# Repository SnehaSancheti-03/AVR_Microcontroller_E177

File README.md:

# AVR_Microcontroller  
**ATmega-Based AVR Controller PCB Design**

---

## 👩‍🎓 Student Information
- **Name:** Sneha Sancheti  
- **Roll No:** E177  

---

## 📌 Project Overview
This project presents the design and development of a complete **ATmega-based AVR microcontroller controller board** using KiCad PCB design tools.

The board integrates all essential subsystems required for embedded system prototyping, including regulated power supply, clock generation, reset circuitry, programming interface, sensor connectivity, communication interface, and peripheral headers.

The design enables reliable deployment of AVR-based embedded applications in academic and experimental environments.

---

## 🎯 Objectives
- Design a standalone AVR microcontroller PCB  
- Implement stable regulated power supply  
- Provide programming and communication interfaces  
- Support sensor and actuator connectivity  
- Integrate LCD display interface  
- Produce manufacturable PCB layout  

---

## 🧩 System Architecture
The AVR controller board is composed of the following functional blocks:

- Power Supply Section  
- ATmega Microcontroller Core  
- Clock Circuit  
- Reset Circuit  
- Programming Interface (ISP)  
- Sensor Interfaces  
- Display Interface  
- Communication Interface  
- Expansion Headers  

These modules together form a complete embedded controller platform.

---

## 🔌 Hardware Design

### ATmega Microcontroller Core
The central controller is an ATmega AVR microcontroller configured with decoupling capacitors and I/O breakout headers to support external peripherals and modules.

---

### Power Supply Section
The circuit includes a regulated DC supply stage providing stable operating voltage to the microcontroller and connected peripherals. Filtering and decoupling ensure noise-free operation.

---

### Clock Circuit
An external crystal oscillator with load capacitors provides precise timing required for accurate AVR operation.

---

### Reset Circuit
A hardware reset push-button with pull-up configuration enables proper initialization and safe restart of the microcontroller.

---

### Programming Interface
The design includes an AVR ISP programming header enabling in-system firmware uploading without removing the microcontroller from the PCB.

---

## 📟 Peripheral Interfaces

### Sensor Interfaces
The controller supports interfacing of multiple analog and digital sensors through ADC and GPIO pins, including:

- Flex sensor  
- Pressure sensor  
- Ultrasonic sensor  
- IR sensor modules  
- Analog sensor modules  

---

### Display Interface
A standard **16×2 LCD interface** is provided for real-time data visualization and system feedback.

---

### Communication Interface
UART serial communication support enables connection to external systems such as:

- USB-to-Serial converters  
- Computers  
- Embedded communication modules  

---

### Actuator / Output Interfaces
The board supports control of external devices such as:

- Motors  
- Relays  
- Buzzers  
- LEDs  
- Driver modules  

---

## 🖥️ Design Output
The project deliverables include:

- Complete schematic design  
- PCB layout  
- Gerber manufacturing files  
- Drill files  
- Component mapping files  

---

## 🛠️ Tools Used
- **KiCad** – Schematic and PCB design  
- AVR microcontroller architecture references  
- Standard electronic components  

---

## 📁 Repository Contents

Drill_files/
Gerber_Files/
AVR_Controller_E177_Sneha.kicad_pcb
AVR_Controller_E177_Sneha.kicad_sch
AVR_Controller_E177_Sneha.kicad_prl
AVR_Controller_E177_Sneha.kicad_pro

---

## 🧪 Applications
The designed AVR controller board can be used for:

- Embedded systems learning  
- Sensor interfacing experiments  
- Robotics control platforms  
- Data acquisition systems  
- Automation prototypes  
- IoT hardware projects  

---

## ✅ Conclusion
A complete AVR microcontroller controller board was successfully designed integrating power management, processing, communication, and interfacing subsystems.

The PCB layout is compact, functional, and suitable for embedded system prototyping and academic applications.

---

## 📚 Reference
ATmega AVR architecture and interfacing concepts as illustrated in the assignment design sheet.   

---

## 👤 Author
**Sneha Sancheti**  
Roll No: E177  

---

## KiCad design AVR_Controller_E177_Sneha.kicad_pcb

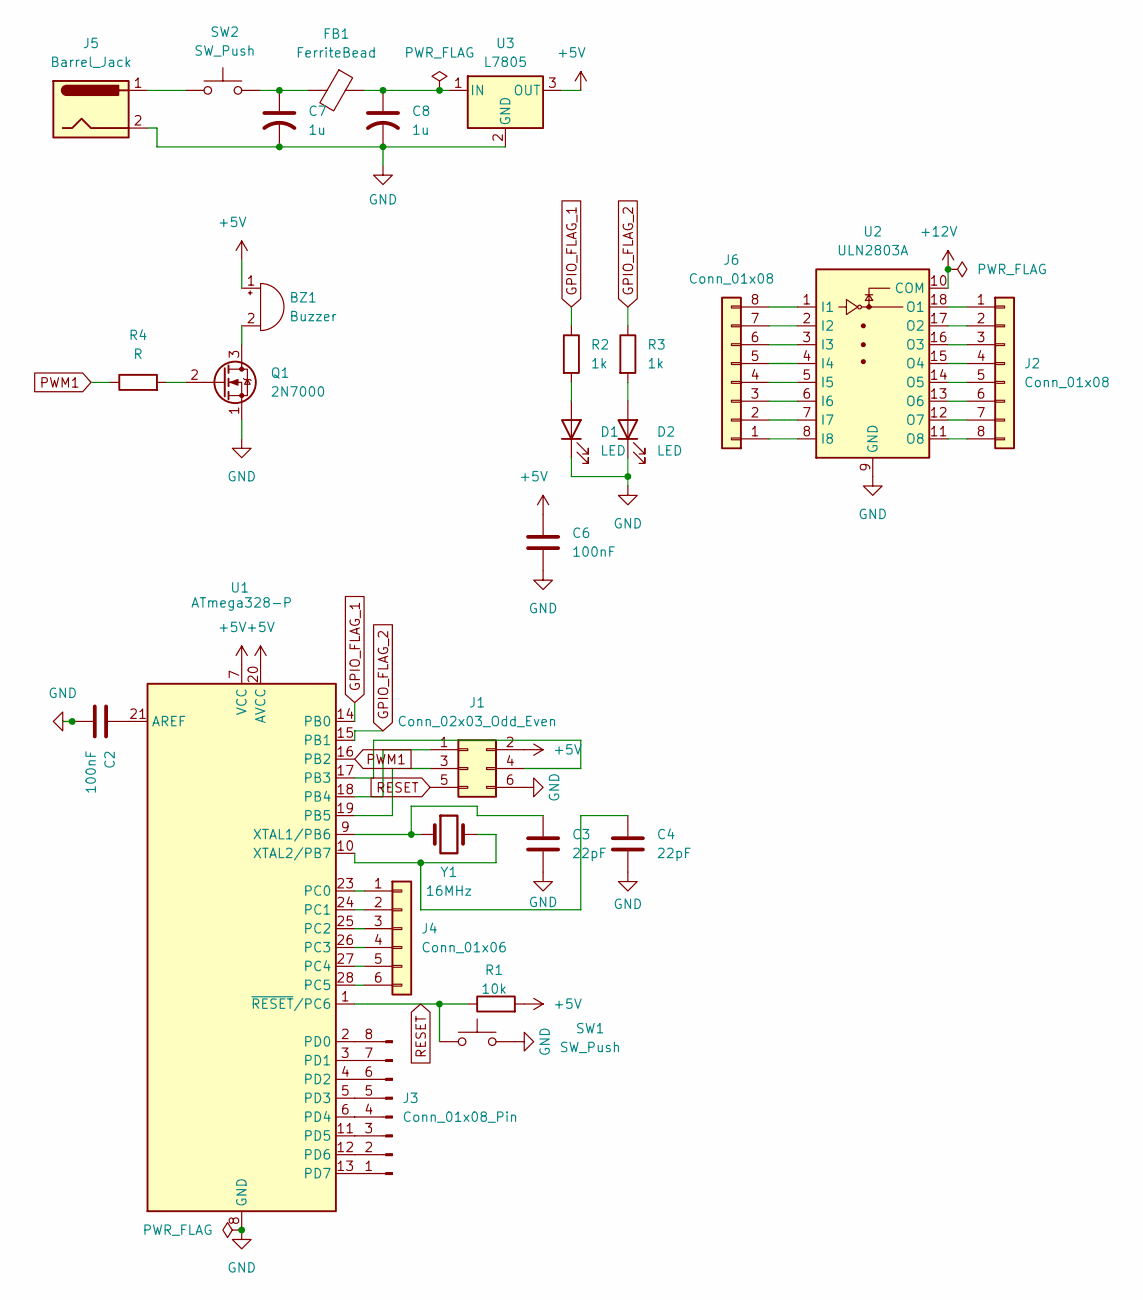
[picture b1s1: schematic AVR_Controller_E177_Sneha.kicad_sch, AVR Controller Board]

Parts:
BZ1: Buzzer; Buzzer_15x7.5RM7.6
C2, C6: 100nF; C_Disc_D5.0mm_W2.5mm_P5.00mm
C3, C4: 22pF; C_Disc_D5.0mm_W2.5mm_P5.00mm
C7, C8: 1u; C_Disc_D5.0mm_W2.5mm_P5.00mm
D1, D2: LED; LED_D3.0mm
FB1: FerriteBead; LairdTech_28C0236-0JW-10
J1: Conn_02x03_Odd_Even; PinHeader_2x03_P2.54mm_Vertical
J2, J6: Conn_01x08; PinHeader_1x08_P2.54mm_Vertical
J3: Conn_01x08_Pin; PinHeader_1x08_P2.54mm_Vertical
J4: Conn_01x06; PinHeader_1x06_P2.54mm_Vertical
J5: Barrel_Jack; BarrelJack_Horizontal
Q1: 2N7000; TO-92_Inline
R1: 10k; R_Axial_DIN0207_L6.3mm_D2.5mm_P10.16mm_Horizontal
R2, R3: 1k; R_Axial_DIN0207_L6.3mm_D2.5mm_P10.16mm_Horizontal
R4: R; R_Axial_DIN0207_L6.3mm_D2.5mm_P10.16mm_Horizontal
SW1, SW2: SW_Push; SW_PUSH_6mm
U1: ATmega328-P; DIP-28_W7.62mm
U2: ULN2803A; SOIC-18W_7.5x11.6mm_P1.27mm
U3: L7805; TO-220-3_Vertical
Y1: 16MHz; Crystal_HC49-4H_Vertical

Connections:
+5V: BZ1.1 (+), C6.2, J1.2, R1.2, U1.7 (VCC), U1.20 (AVCC), U3.3 (OUT)
+12V: U2.10 (COM)
GND: C2.1, C3.2, C4.2, C6.1, C7.2, C8.2, D1.1 (K), D2.1 (K), J1.6, J5.2, Q1.1 (S), SW1.2, U1.8 (GND), U1.22 (GND), U2.9 (GND), U3.2 (GND)
GPIO_FLAG_1: R2.1, U1.14 (PB0)
GPIO_FLAG_2: R3.1, U1.15 (PB1)
unnamed: BZ1.2 (-), Q1.3 (D)
unnamed: C7.1, FB1.2, SW2.2
unnamed: D1.2 (A), R2.2
unnamed: D2.2 (A), R3.2
unnamed: J1.1, U1.18 (PB4)
unnamed: J1.3, U1.19 (PB5)
unnamed: J1.4, U1.17 (PB3)
unnamed: J2.1, U2.18 (O1)
unnamed: J2.2, U2.17 (O2)
unnamed: J2.3, U2.16 (O3)
unnamed: J2.4, U2.15 (O4)
unnamed: J2.5, U2.14 (O5)
unnamed: J2.6, U2.13 (O6)
unnamed: J2.7, U2.12 (O7)
unnamed: J2.8, U2.11 (O8)
unnamed: J3.1, U1.13 (PD7)
unnamed: J3.2, U1.12 (PD6)
unnamed: J3.3, U1.11 (PD5)
unnamed: J3.4, U1.6 (PD4)
unnamed: J3.5, U1.5 (PD3)
unnamed: J3.6, U1.4 (PD2)
unnamed: J3.7, U1.3 (PD1)
unnamed: J3.8, U1.2 (PD0)
unnamed: J4.1, U1.23 (PC0)
unnamed: J4.2, U1.24 (PC1)
unnamed: J4.3, U1.25 (PC2)
unnamed: J4.4, U1.26 (PC3)
unnamed: J4.5, U1.27 (PC4)
unnamed: J4.6, U1.28 (PC5)
unnamed: J5.1, SW2.1
unnamed: J6.1, U2.8 (I8)
unnamed: J6.2, U2.7 (I7)
unnamed: J6.3, U2.6 (I6)
unnamed: J6.4, U2.5 (I5)
unnamed: J6.5, U2.4 (I4)
unnamed: J6.6, U2.3 (I3)
unnamed: J6.7, U2.2 (I2)
unnamed: J6.8, U2.1 (I1)
unnamed: Q1.2 (G), R4.2
unnamed: C2.2, U1.21 (AREF)
unnamed: C3.1, U1.9 (XTAL1/PB6), Y1.1
unnamed: C4.1, U1.10 (XTAL2/PB7), Y1.2
unnamed: C8.1, FB1.1, U3.1 (IN)
PWM1: R4.1, U1.16 (PB2)
RESET: J1.5, R1.1, SW1.1, U1.1 (~RESET/PC6)

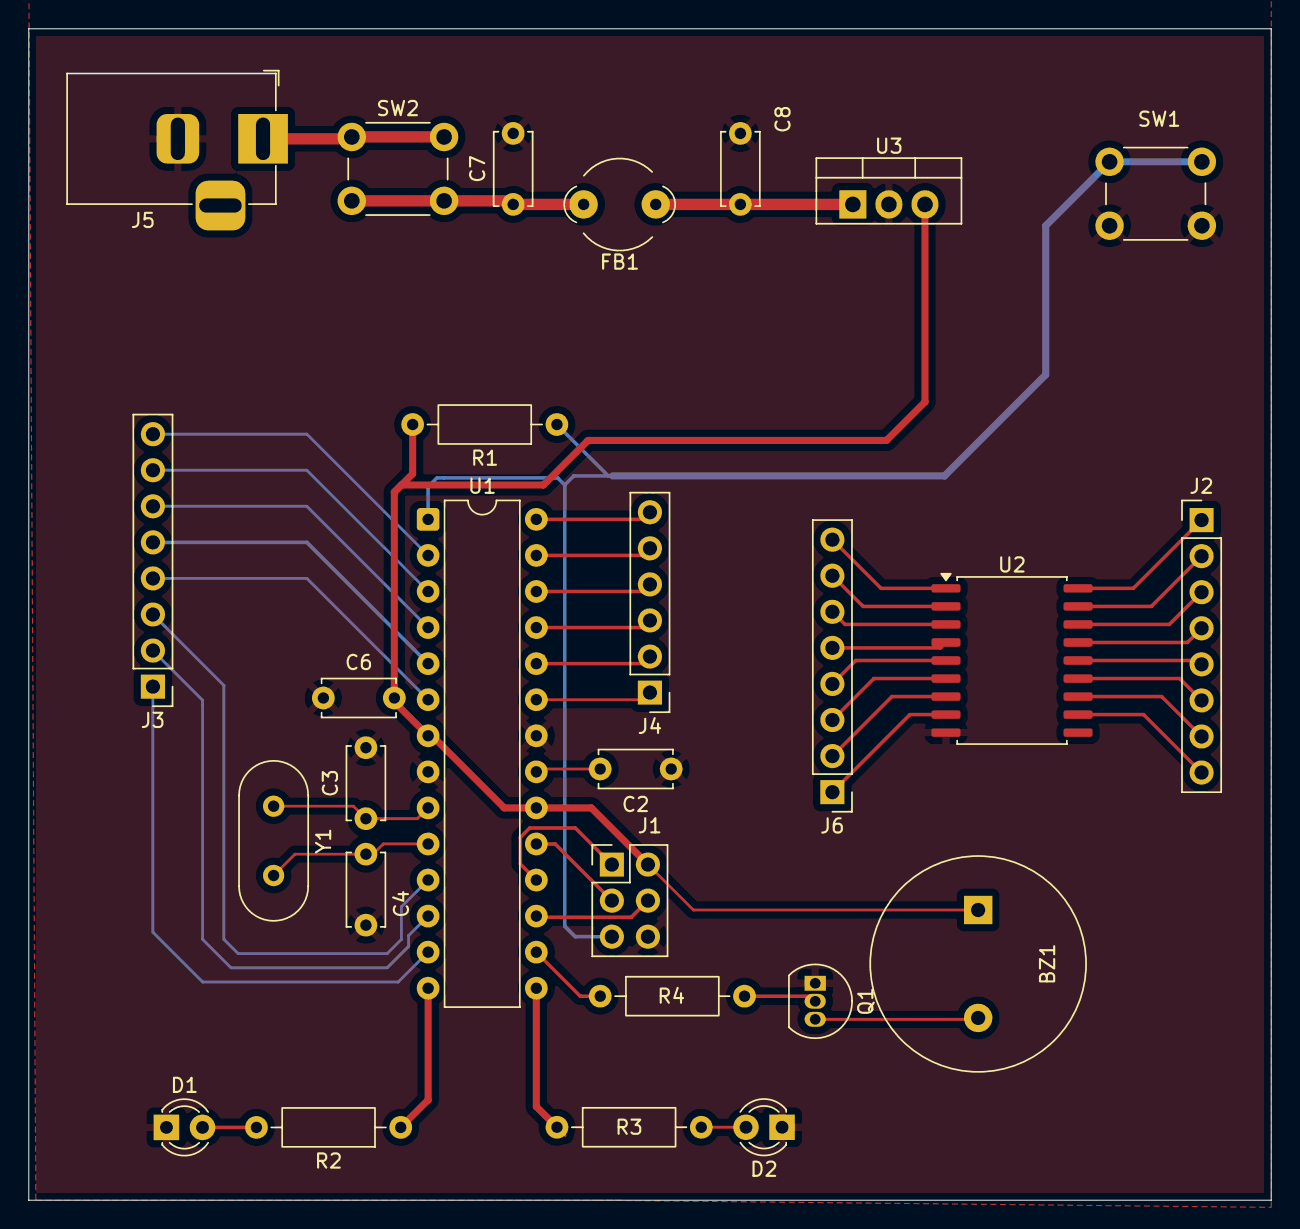
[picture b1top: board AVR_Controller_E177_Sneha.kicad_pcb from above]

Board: 2 copper layers, 87.5 x 82.5 mm, 27 parts (0 on the bottom side), 49 nets.
